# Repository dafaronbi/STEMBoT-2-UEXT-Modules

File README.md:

# STEMBoT-2-UEXT-Modules

## PREPARED BY
### Dean Harris, Daniel Faronbi,
### Dylan Schufeldt, Houd Al-Shariyani

The STEMBoT 2 (SB2)  is a mobile robotic platform and successor to SBI’s first product, the CEENBoT, which 
saw success in schools throughout the United States. The development goal of the SB2 project is to create a 
modular and easy-to-use product that will be used as a platform for teaching STEM related skills to students 
from kindergarten to the university level. The SB2 will accomplish this goal by incorporating the Python programming 
language into embedded systems development. The SB2 also uses plug-and-play UEXT modules for customizability and increased functionality.

The goal of this Capstone team will be to develop seven UEXT modules with a Python library for use by STEMBoT Incorporated. This document
will go over general requirements for the batch of UEXT modules as well as the specifications for each individual module. Necessary changes
to these specifications should be requested prior to completion of the project.

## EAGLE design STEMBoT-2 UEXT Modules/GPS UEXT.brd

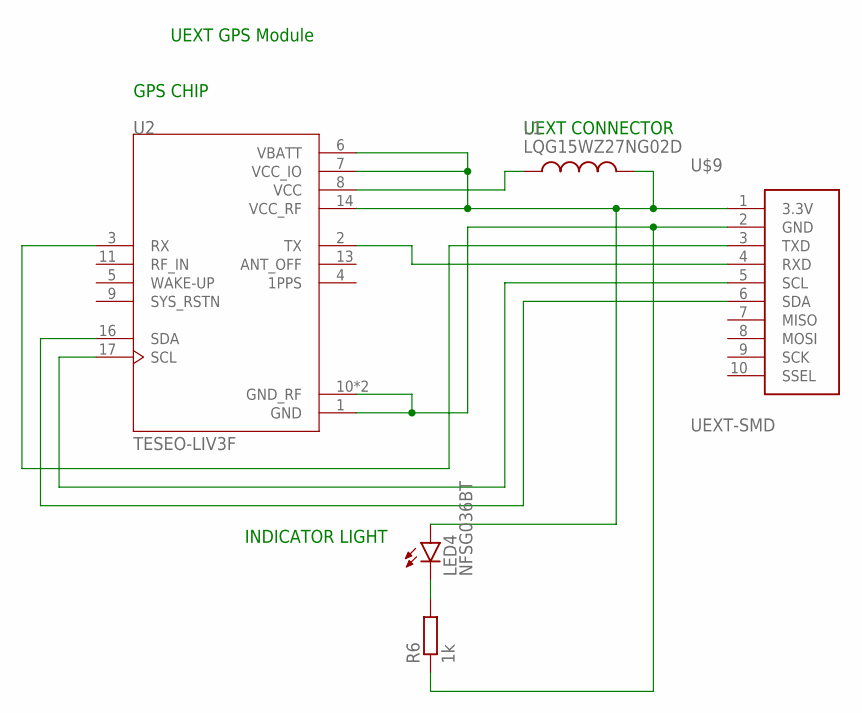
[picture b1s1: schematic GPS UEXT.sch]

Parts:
L1: LQG15WZ27NG02D; INDC1006X60N
LED4: NFSG036BT
R6: 1k; M1206
U2: TESEO-LIV3F
U$9: UEXT-SMD

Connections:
unnamed: U2.2 (TX), U$9.4 (RXD)
unnamed: U2.3 (RX), U$9.3 (TXD)
unnamed: L1.1, U2.8 (VCC)
unnamed: R6.1, U2.1 (GND), U2.10 (GND_RF), U2.12 (GND_RF), U$9.2 (GND)
unnamed: L1.2, LED4.A, U2.6 (VBATT), U2.7 (VCC_IO), U2.14 (VCC_RF), U$9.1 (3.3V)
unnamed: U2.17 (SCL), U$9.5 (SCL)
unnamed: U2.16 (SDA), U$9.6 (SDA)
unnamed: LED4.C, R6.2

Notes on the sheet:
GPS CHIP
UEXT CONNECTOR
INDICATOR LIGHT
UEXT GPS Module

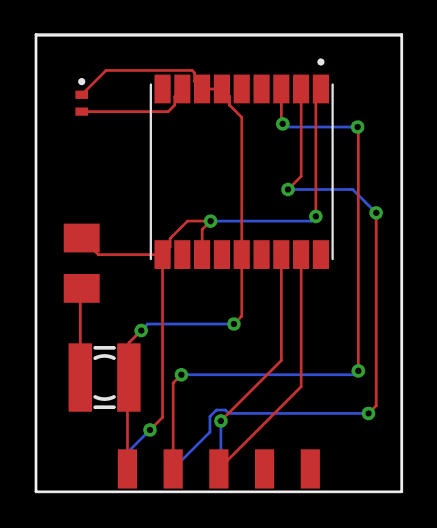
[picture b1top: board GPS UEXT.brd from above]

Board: 2 copper layers, 20.3 x 25.3 mm, 5 parts (0 on the bottom side), 8 nets.

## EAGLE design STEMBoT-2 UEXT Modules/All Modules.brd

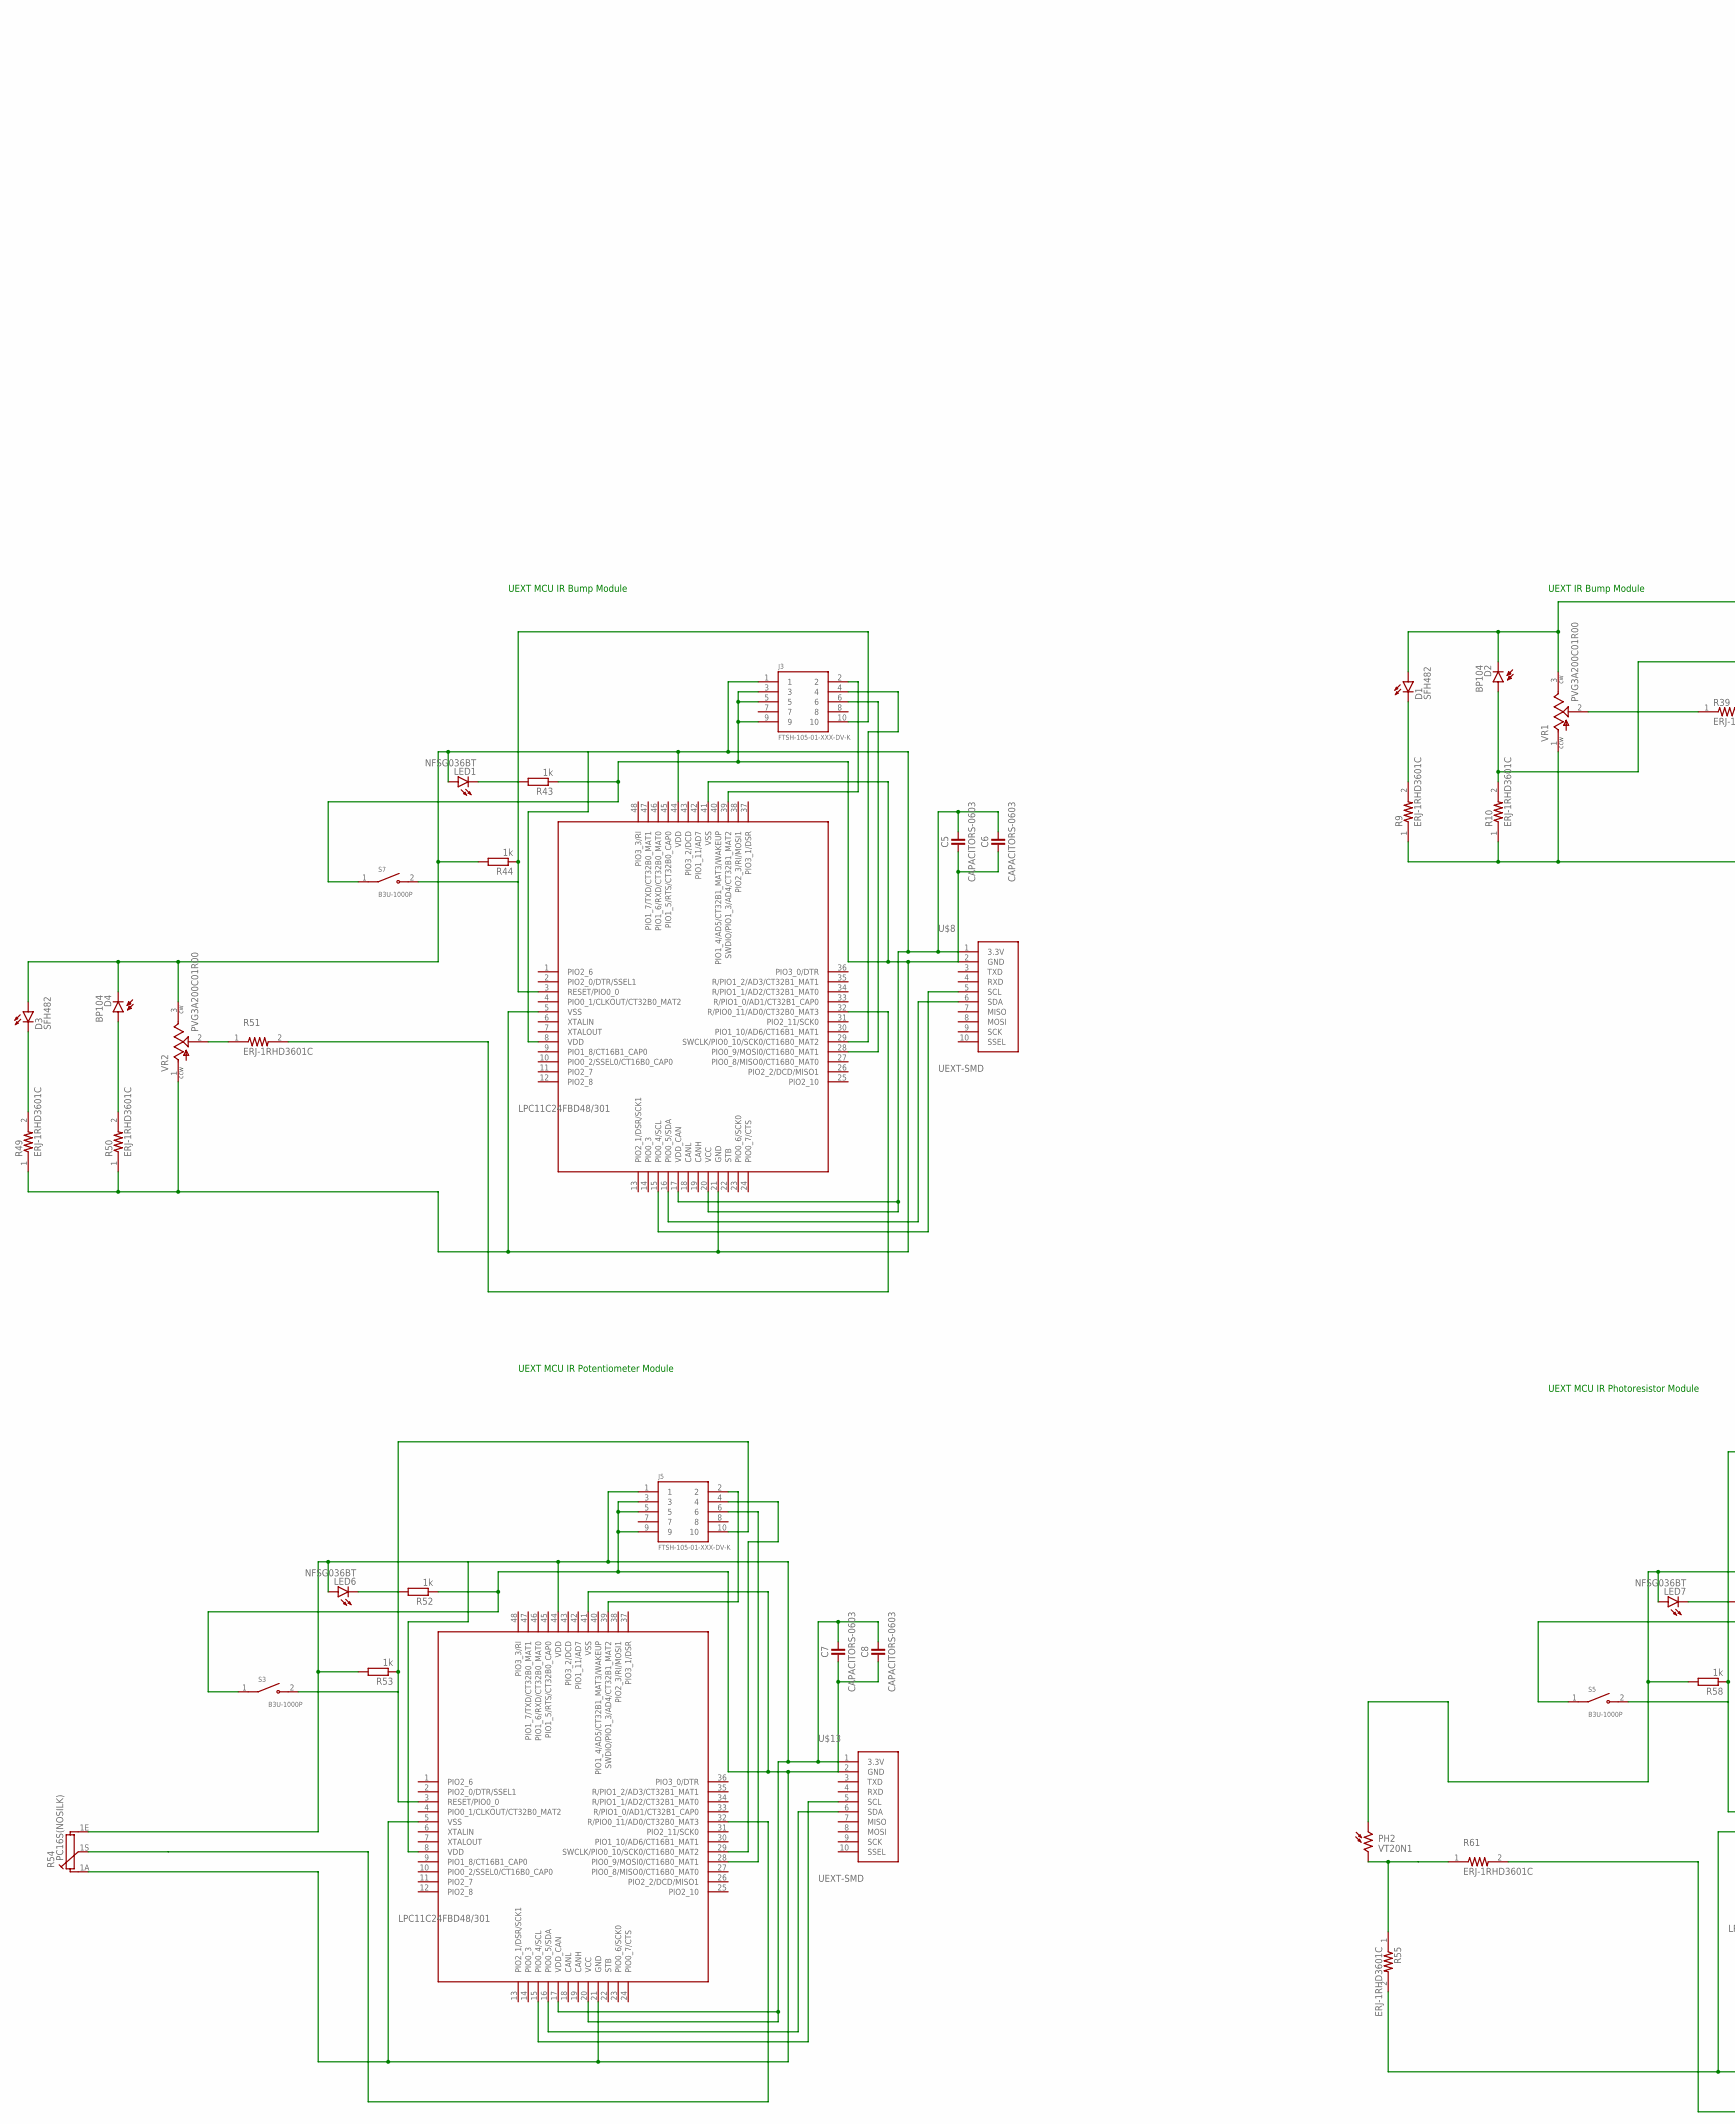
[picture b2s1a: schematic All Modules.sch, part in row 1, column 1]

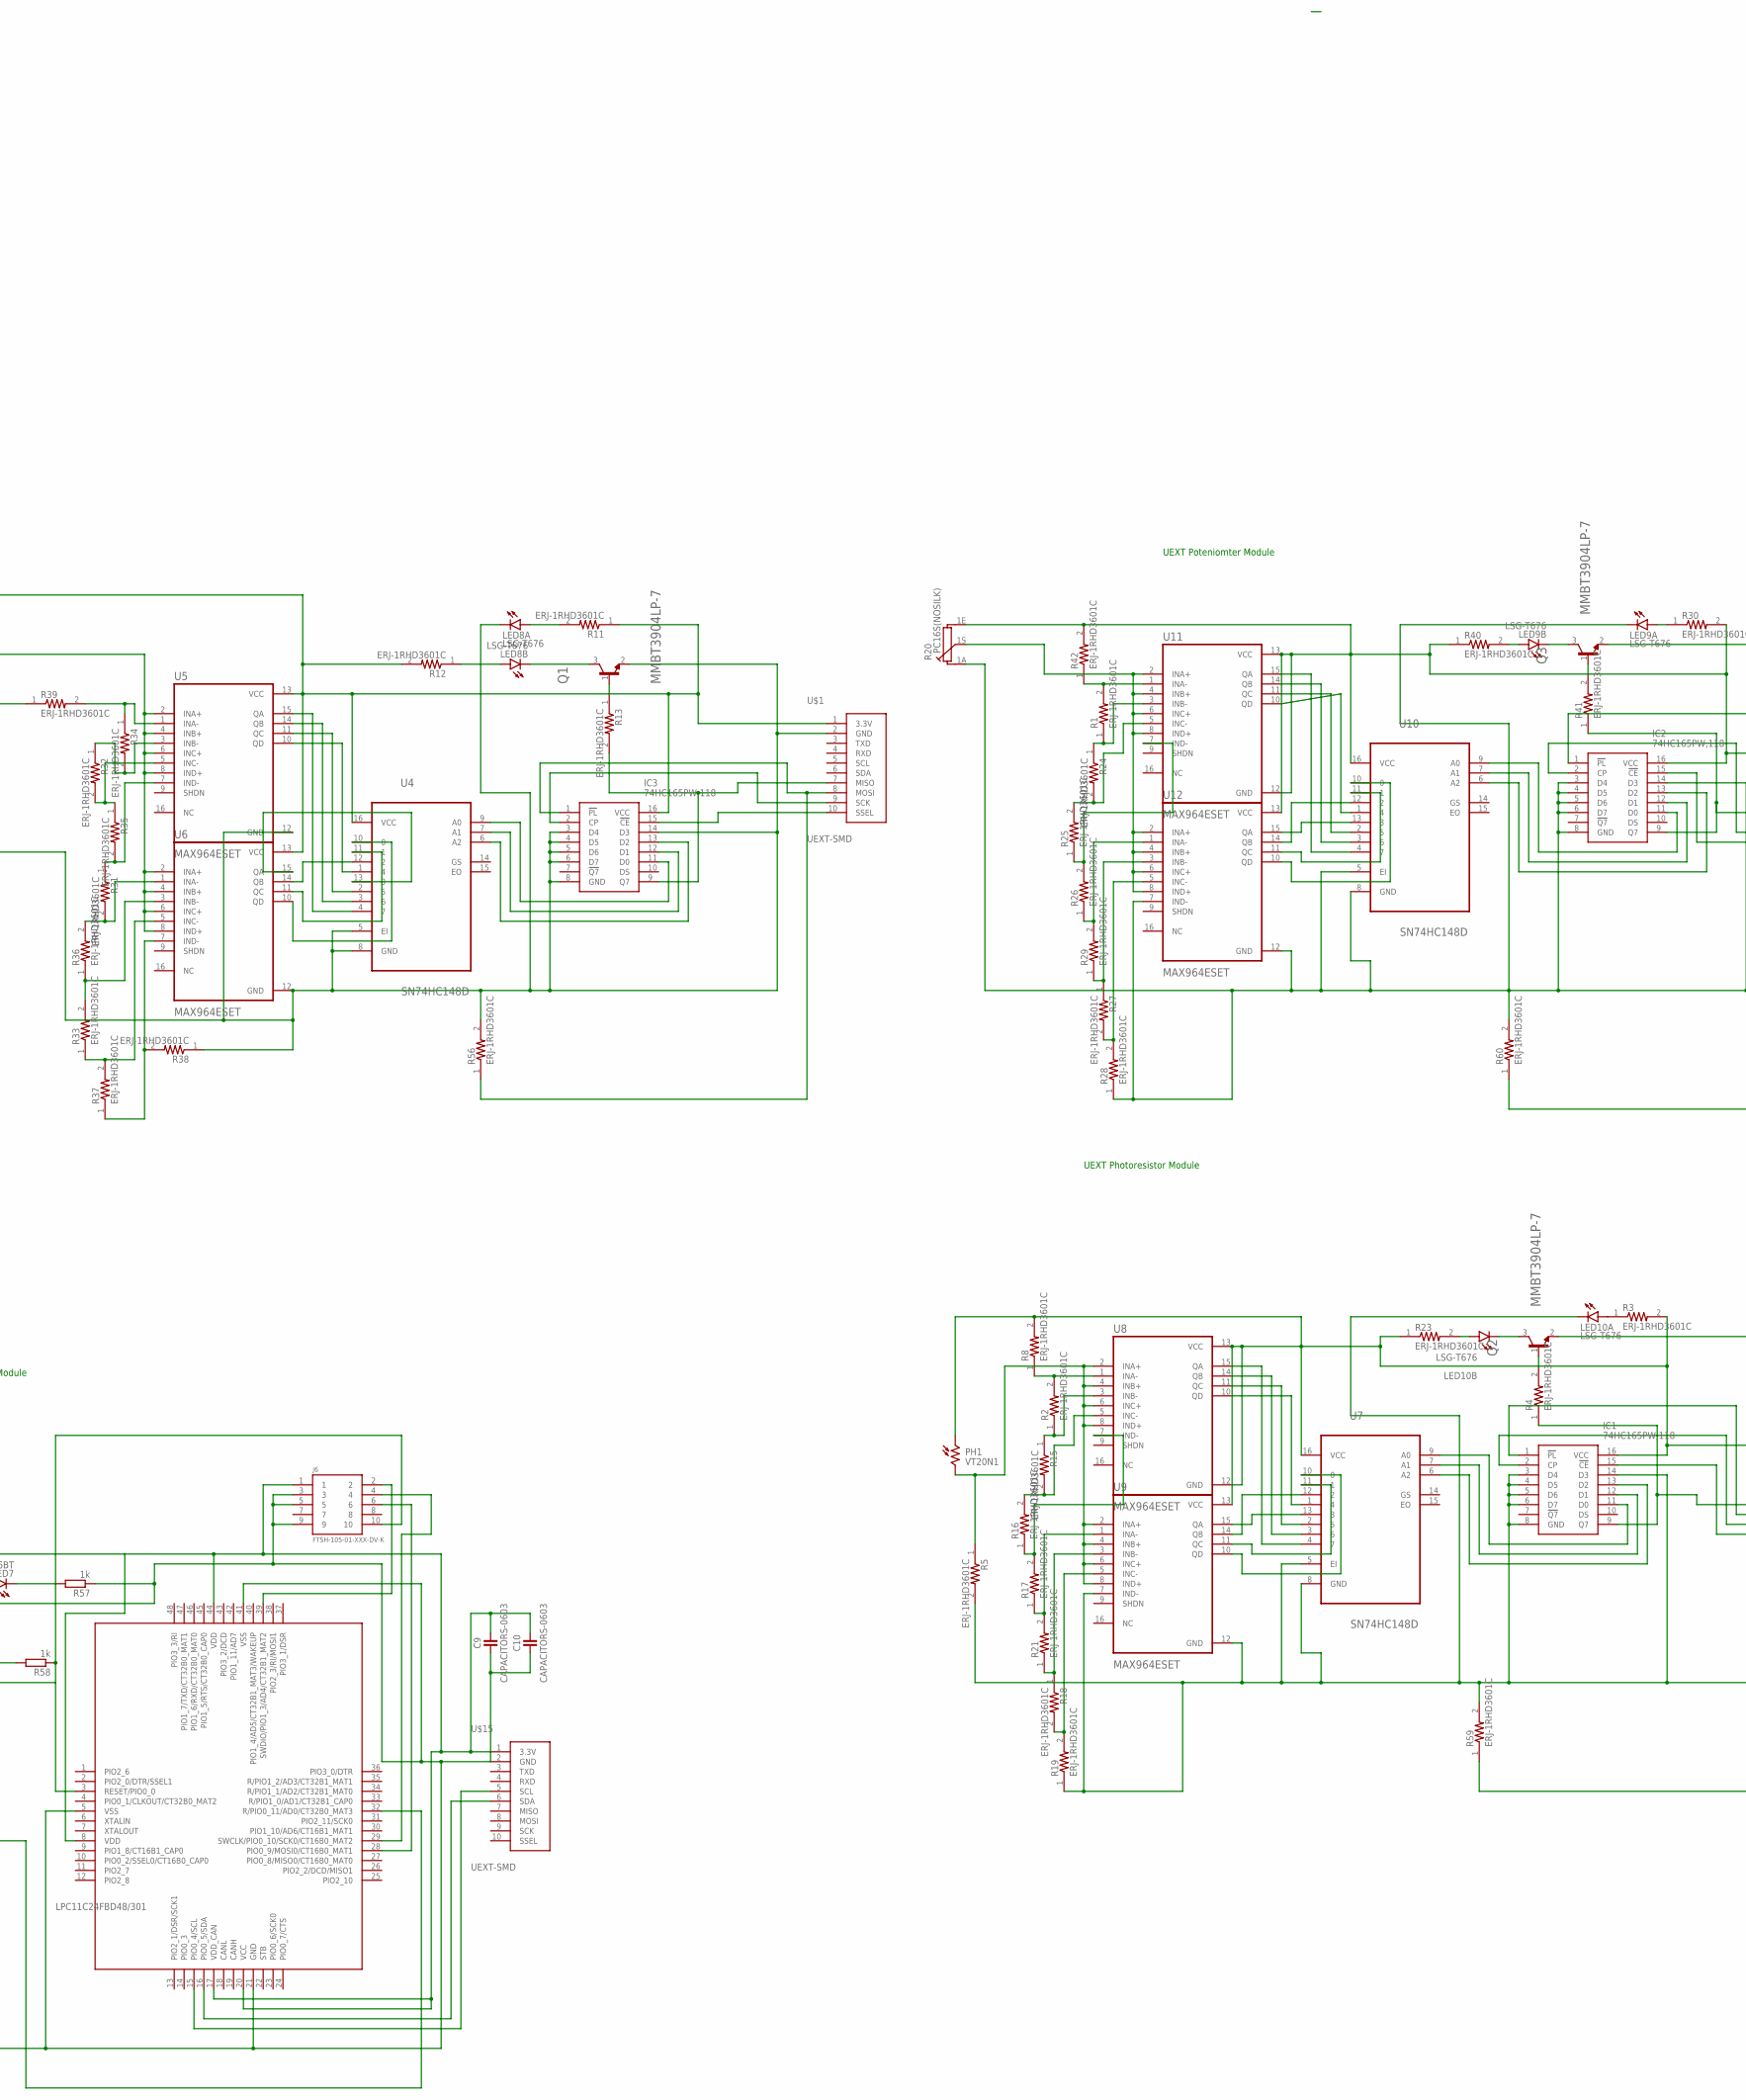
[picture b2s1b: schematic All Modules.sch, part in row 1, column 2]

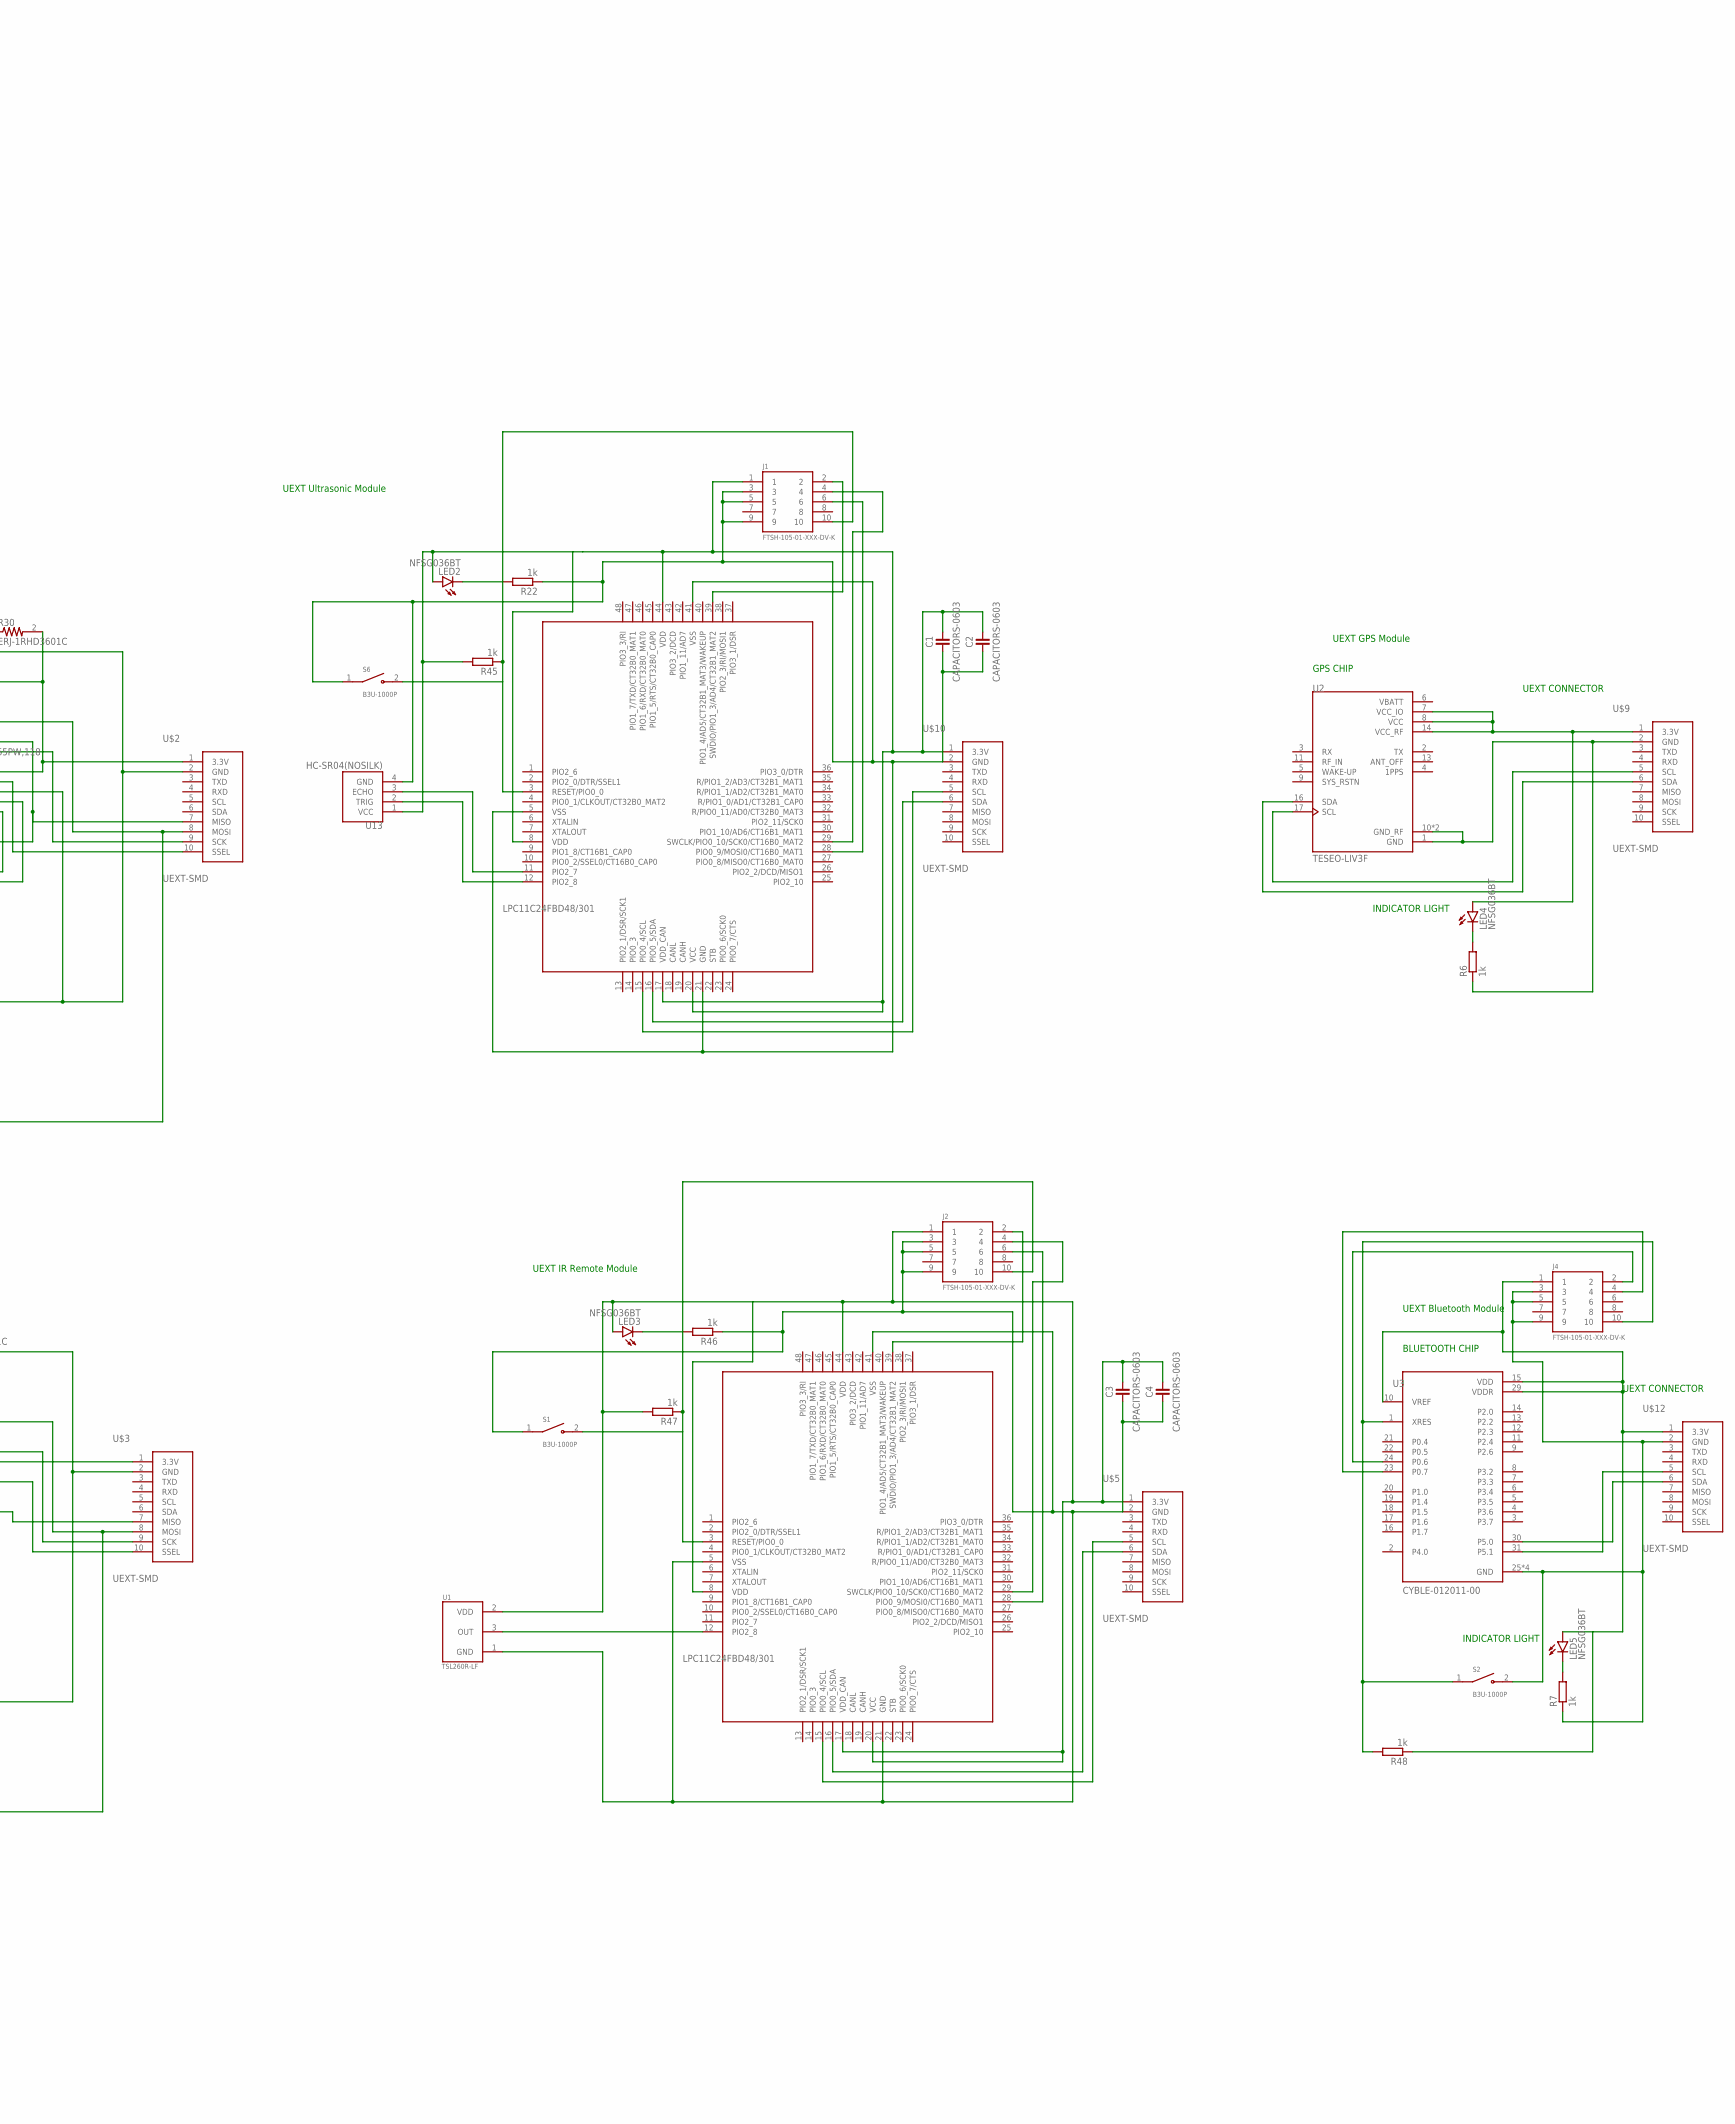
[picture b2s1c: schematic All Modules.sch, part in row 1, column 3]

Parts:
C1, C2, C3, C4, C5, C6, C7, C8, C9, C10: CAPACITORS-0603; C0603
D1, D3: SFH482
D2, D4: BP104
IC1, IC2, IC3: 74HC165PW,118; SOP65P640X110-16N
J1, J2, J3, J4, J5, J6: FTSH-105-01-XXX-DV-K
LED1, LED2, LED3, LED4, LED5, LED6, LED7: NFSG036BT
LED8, LED9, LED10: LSG-T676; P-LCC4-0
PH1, PH2: VT20N1; TO46-VT200
Q1, Q2, Q3: MMBT3904LP-7; DFN101X61X53-3N
R1, R2, R3, R4, R5, R8, R9, R10, R11, R12, R13, R15, R16, R17, R18, R19, R21, R23, R24, R25, R26, R27, R28, R29, R30, R31, R32, R33, R34, R35, R36, R37, R38, R39, R40, R41, R42, R49, R50, R51, R55, R56, R59, R60, R61: ERJ-1RHD3601C; RESC0603X26N
R6, R7, R22, R43, R44, R45, R46, R47, R48, R52, R53, R57, R58: 1k; M1206
R20, R54: PC16S(NOSILK)
S1, S2, S3, S5, S6, S7: B3U-1000P; SW_B3U-1000P
U1: TSL260R-LF; XDCR_TSL260R-LF
U2: TESEO-LIV3F
U3: CYBLE-012011-00; XCVR_CYBLE-012011-00
U4, U7, U10: SN74HC148D; SOIC127P600X175-16N
U5, U6, U8, U9, U11, U12: MAX964ESET; SOIC127P600X175-16N
U13: HC-SR04(NOSILK); XCVR_HC-SR04(NOSILK)
U$1, U$2, U$3, U$5, U$8, U$9, U$10, U$12, U$13, U$15: UEXT-SMD
U$4, U$6, U$7, U$11, U$14: LPC11C24FBD48/301; QFP50P900X900X160-48N
VR1, VR2: PVG3A200C01R00; TRIM_PVG3A200C01R00

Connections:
unnamed: C1.1, C2.1, J1.3, J1.5, J1.9, R22.1, S6.1, U13.4 (GND), U$7.5 (VSS), U$7.21 (GND), U$7.41 (VSS), U$10.2 (GND)
unnamed: D1.A, D2.K (C), IC3.16 (VCC), R11.1, R12.2, U4.16 (VCC), U5.13 (VCC), U6.13 (VCC), U$1.1 (3.3V), VR1.3 (CW)
unnamed: LED2.C, R22.2
unnamed: Q3.1 (B), R41.2
unnamed: LED9.2 (A), R30.1
unnamed: C3.1, C4.1, J2.3, J2.5, J2.9, R46.1, S1.1, U1.1 (GND), U$4.5 (VSS), U$4.21 (GND), U$4.41 (VSS), U$5.2 (GND)
unnamed: IC3.15 (!CE), U$1.10 (SSEL)
unnamed: Q2.1 (B), R4.2
unnamed: LED10.2 (A), R3.1
unnamed: LED10.3 (C), Q2.3 (C)
unnamed: IC1.13 (D2), U7.6 (A2)
unnamed: PH1.2, R5.1, U8.2 (INA+), U8.4 (INB+), U8.6 (INC+), U8.8 (IND+), U9.2 (INA+), U9.4 (INB+), U9.6 (INC+), U9.8 (IND+)
unnamed: IC1.15 (!CE), U$3.10 (SSEL)
unnamed: IC3.2 (CP), U$1.9 (SCK)
unnamed: LED9.3 (C), Q3.3 (C)
unnamed: IC1.9 (Q7), R4.1, U$3.7 (MISO)
unnamed: IC2.11 (D0), U10.9 (A0)
unnamed: LED10.4 (A), R23.2
unnamed: IC1.11 (D0), U7.9 (A0)
unnamed: IC1.12 (D1), U7.7 (A1)
unnamed: R6.1, U2.1 (GND), U2.10 (GND_RF), U2.12 (GND_RF), U$9.2 (GND)
unnamed: LED4.A, U2.7 (VCC_IO), U2.8 (VCC), U2.14 (VCC_RF), U$9.1 (3.3V)
unnamed: U2.17 (SCL), U$9.5 (SCL)
unnamed: U2.16 (SDA), U$9.6 (SDA)
unnamed: LED4.C, R6.2
unnamed: J4.1, LED5.A, R48.1, U3.10 (VREF), U3.15 (VDD), U3.29 (VDDR), U$12.1 (3.3V)
unnamed: U3.30 (P5.0), U$12.6 (SDA)
unnamed: U3.31 (P5.1), U$12.5 (SCL)
unnamed: J4.3, J4.5, J4.9, R7.1, S2.2, U3.25 (GND), U3.26 (GND), U3.27 (GND), U3.28 (GND), U$12.2 (GND)
unnamed: LED5.C, R7.2
unnamed: D1.K (C), R9.2
unnamed: LED8.2 (A), R11.2
unnamed: R2.1, R15.1, U8.3 (INB-)
unnamed: R15.2, R16.2, U8.5 (INC-)
unnamed: R16.1, R17.2, U8.7 (IND-)
unnamed: R17.1, R21.2, U9.1 (INA-)
unnamed: R18.1, R21.1, U9.3 (INB-)
unnamed: R18.2, R19.2, U9.5 (INC-)
unnamed: IC1.3 (D4), IC1.4 (D5), IC1.5 (D6), IC1.6 (D7), IC1.8 (GND), IC1.14 (D3), LED10.1 (C), Q2.2 (E), R5.2, R19.1, R59.2, U7.5 (EI), U7.8 (GND), U9.7 (IND-), U9.12 (GND), U$3.2 (GND)
unnamed: U7.4 (7), U8.15 (QA)
unnamed: U7.3 (6), U8.14 (QB)
unnamed: U7.2 (5), U8.11 (QC)
unnamed: U7.1 (4), U8.10 (QD)
unnamed: U7.13 (3), U9.15 (QA)
unnamed: U7.12 (2), U9.14 (QB)
unnamed: LED8.4 (A), R12.1
unnamed: LED8.3 (C), Q1.3 (C)
unnamed: U7.11 (1), U9.11 (QC)
unnamed: U7.10 (0), U9.10 (QD)
unnamed: R2.2, R8.1, U8.1 (INA-)
unnamed: IC1.16 (VCC), PH1.1, R3.2, R8.2, R23.1, U7.16 (VCC), U8.12 (GND), U8.13 (VCC), U9.13 (VCC), U$3.1 (3.3V)
unnamed: IC1.2 (CP), U$3.9 (SCK)
unnamed: IC2.12 (D1), U10.7 (A1)
unnamed: IC2.13 (D2), U10.6 (A2)
unnamed: IC3.3 (D4), IC3.4 (D5), IC3.5 (D6), IC3.6 (D7), IC3.8 (GND), IC3.14 (D3), LED8.1 (C), Q1.2 (E), R9.1, R10.1, R38.1, R56.2, U4.5 (EI), U4.8 (GND), U5.12 (GND), U6.12 (GND), U$1.2 (GND), VR1.1 (CCW)
unnamed: IC2.9 (Q7), R41.1, U$2.7 (MISO)
unnamed: LED9.4 (A), R40.2
unnamed: R1.1, R24.1, U11.3 (INB-)
unnamed: R24.2, R25.2, U11.5 (INC-)
unnamed: R25.1, R26.2, U11.7 (IND-)
unnamed: R26.1, R29.2, U12.1 (INA-)
unnamed: R27.1, R29.1, U12.3 (INB-)
unnamed: R27.2, R28.2, U12.5 (INC-)
unnamed: IC2.3 (D4), IC2.4 (D5), IC2.5 (D6), IC2.6 (D7), IC2.8 (GND), IC2.14 (D3), LED9.1 (C), Q3.2 (E), R20.1A, R28.1, R60.2, U10.5 (EI), U10.8 (GND), U12.7 (IND-), U12.12 (GND), U$2.2 (GND)
unnamed: U10.4 (7), U11.15 (QA)
unnamed: U10.3 (6), U11.14 (QB)
unnamed: U10.2 (5), U11.11 (QC)
unnamed: U10.1 (4), U11.10 (QD)
unnamed: U10.13 (3), U12.15 (QA)
unnamed: D2.A, R10.2, U5.2 (INA+), U5.4 (INB+), U5.6 (INC+), U5.8 (IND+), U6.2 (INA+), U6.4 (INB+), U6.6 (INC+), U6.8 (IND+)
unnamed: Q1.1 (B), R13.1
unnamed: U10.12 (2), U12.14 (QB)
unnamed: IC3.11 (D0), U4.9 (A0)
unnamed: IC3.12 (D1), U4.7 (A1)
unnamed: IC3.13 (D2), U4.6 (A2)
unnamed: IC3.9 (Q7), R13.2, U$1.7 (MISO)
unnamed: U10.11 (1), U12.11 (QC)
unnamed: R34.1, R39.2, U5.1 (INA-)
unnamed: U$7.16 (PIO0_5/SDA), U$10.6 (SDA)
unnamed: U$7.15 (PIO0_4/SCL), U$10.5 (SCL)
unnamed: R32.1, R34.2, U5.3 (INB-)
unnamed: J1.4, U$7.29 (SWCLK/PIO0_10/SCK0/CT16B0_MAT2)
unnamed: J1.2, U$7.39 (SWDIO/PIO1_3/AD4/CT32B1_MAT2)
unnamed: J1.6, U$7.28 (PIO0_9/MOSI0/CT16B0_MAT1)
unnamed: U13.2 (TRIG), U$7.12 (PIO2_8)
unnamed: U13.3 (ECHO), U$7.11 (PIO2_7)
unnamed: R32.2, R35.1, U5.5 (INC-)
unnamed: R31.1, R35.2, U5.7 (IND-)
unnamed: R31.2, R36.2, U6.1 (INA-)
unnamed: R33.2, R36.1, U6.3 (INB-)
unnamed: R33.1, R37.2, U6.5 (INC-)
unnamed: R37.1, R38.2, U6.7 (IND-)
unnamed: U4.4 (7), U5.15 (QA)
unnamed: U4.3 (6), U5.14 (QB)
unnamed: U4.2 (5), U5.11 (QC)
unnamed: U4.1 (4), U5.10 (QD)
unnamed: U4.13 (3), U6.15 (QA)
unnamed: U4.12 (2), U6.14 (QB)
unnamed: U4.11 (1), U6.11 (QC)
unnamed: U4.10 (0), U6.10 (QD)
unnamed: U10.10 (0), U12.10 (QD)
unnamed: R1.2, R42.1, U11.1 (INA-)
unnamed: IC2.15 (!CE), U$2.10 (SSEL)
unnamed: IC2.2 (CP), U$2.9 (SCK)
unnamed: IC2.16 (VCC), R20.1E, R30.2, R40.1, R42.2, U10.16 (VCC), U11.12 (GND), U11.13 (VCC), U12.13 (VCC), U$2.1 (3.3V)
unnamed: R20.1S, U11.2 (INA+), U11.4 (INB+), U11.6 (INC+), U11.8 (IND+), U12.2 (INA+), U12.4 (INB+), U12.6 (INC+), U12.8 (IND+)
unnamed: LED6.C, R52.2
unnamed: LED1.C, R43.2
unnamed: J1.10, R45.1, S6.2, U$7.3 (RESET/PIO0_0)
unnamed: C1.2, C2.2, J1.1, LED2.A, R45.2, U13.1 (VCC), U$7.8 (VDD), U$7.17 (VDD_CAN), U$7.20 (VCC), U$7.44 (VDD), U$10.1 (3.3V)
unnamed: J4.10, R48.2, S2.1, U3.1 (XRES)
unnamed: LED3.C, R46.2
unnamed: U$11.16 (PIO0_5/SDA), U$13.6 (SDA)
unnamed: U$4.16 (PIO0_5/SDA), U$5.6 (SDA)
unnamed: U$4.15 (PIO0_4/SCL), U$5.5 (SCL)
unnamed: C3.2, C4.2, J2.1, LED3.A, R47.2, U1.2 (VDD), U$4.8 (VDD), U$4.17 (VDD_CAN), U$4.20 (VCC), U$4.44 (VDD), U$5.1 (3.3V)
unnamed: J2.4, U$4.29 (SWCLK/PIO0_10/SCK0/CT16B0_MAT2)
unnamed: U$6.16 (PIO0_5/SDA), U$8.6 (SDA)
unnamed: J2.2, U$4.39 (SWDIO/PIO1_3/AD4/CT32B1_MAT2)
unnamed: J2.6, U$4.28 (PIO0_9/MOSI0/CT16B0_MAT1)
unnamed: U$6.15 (PIO0_4/SCL), U$8.5 (SCL)
unnamed: U1.3 (OUT), U$4.12 (PIO2_8)
unnamed: J4.2, U3.24 (P0.6)
unnamed: J2.10, R47.1, S1.2, U$4.3 (RESET/PIO0_0)
unnamed: J4.4, U3.23 (P0.7)
unnamed: J3.4, U$6.29 (SWCLK/PIO0_10/SCK0/CT16B0_MAT2)
unnamed: J3.2, U$6.39 (SWDIO/PIO1_3/AD4/CT32B1_MAT2)
unnamed: J3.6, U$6.28 (PIO0_9/MOSI0/CT16B0_MAT1)
unnamed: D3.K (C), R49.2
unnamed: D4.A, R50.2
unnamed: R51.1, VR2.2 (WIPER)
unnamed: J3.10, R44.1, S7.2, U$6.3 (RESET/PIO0_0)
unnamed: R51.2, U$6.32 (R/PIO0_11/AD0/CT32B0_MAT3)
unnamed: C5.1, C6.1, J3.3, J3.5, J3.9, R43.1, R49.1, R50.1, S7.1, U$6.5 (VSS), U$6.21 (GND), U$6.41 (VSS), U$8.2 (GND), VR2.1 (CCW)
unnamed: C5.2, C6.2, D3.A, D4.K (C), J3.1, LED1.A, R44.2, U$6.8 (VDD), U$6.17 (VDD_CAN), U$6.20 (VCC), U$6.44 (VDD), U$8.1 (3.3V), VR2.3 (CW)
unnamed: U$11.15 (PIO0_4/SCL), U$13.5 (SCL)
unnamed: J5.4, U$11.29 (SWCLK/PIO0_10/SCK0/CT16B0_MAT2)
unnamed: J5.2, U$11.39 (SWDIO/PIO1_3/AD4/CT32B1_MAT2)
unnamed: J5.6, U$11.28 (PIO0_9/MOSI0/CT16B0_MAT1)
unnamed: J5.10, R53.1, S3.2, U$11.3 (RESET/PIO0_0)
unnamed: C7.1, C8.1, J5.3, J5.5, J5.9, R52.1, R54.1A, S3.1, U$11.5 (VSS), U$11.21 (GND), U$11.41 (VSS), U$13.2 (GND)
unnamed: R39.1, VR1.2 (WIPER)
unnamed: C9.2, C10.2, J6.1, LED7.A, PH2.1, R58.2, U$14.8 (VDD), U$14.17 (VDD_CAN), U$14.20 (VCC), U$14.44 (VDD), U$15.1 (3.3V)
unnamed: C7.2, C8.2, J5.1, LED6.A, R53.2, R54.1E, U$11.8 (VDD), U$11.17 (VDD_CAN), U$11.20 (VCC), U$11.44 (VDD), U$13.1 (3.3V)
unnamed: LED7.C, R57.2
unnamed: U$14.16 (PIO0_5/SDA), U$15.6 (SDA)
unnamed: U$14.15 (PIO0_4/SCL), U$15.5 (SCL)
unnamed: J6.4, U$14.29 (SWCLK/PIO0_10/SCK0/CT16B0_MAT2)
unnamed: J6.2, U$14.39 (SWDIO/PIO1_3/AD4/CT32B1_MAT2)
unnamed: J6.6, U$14.28 (PIO0_9/MOSI0/CT16B0_MAT1)
unnamed: J6.10, R58.1, S5.2, U$14.3 (RESET/PIO0_0)
unnamed: PH2.2, R55.1, R61.1
unnamed: IC3.1 (!PL), R56.1, U$1.8 (MOSI)
unnamed: R61.2, U$14.32 (R/PIO0_11/AD0/CT32B0_MAT3)
unnamed: C9.1, C10.1, J6.3, J6.5, J6.9, R55.2, R57.1, S5.1, U$14.5 (VSS), U$14.21 (GND), U$14.41 (VSS), U$15.2 (GND)
unnamed: IC1.1 (!PL), R59.1, U$3.8 (MOSI)
unnamed: IC2.1 (!PL), R60.1, U$2.8 (MOSI)
VBATT: U2.6 (VBATT)

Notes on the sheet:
UEXT Ultrasonic Module
GPS CHIP
UEXT CONNECTOR
INDICATOR LIGHT
UEXT GPS Module
BLUETOOTH CHIP
UEXT Bluetooth Module
UEXT Photoresistor Module
UEXT Poteniomter Module
UEXT IR Remote Module
UEXT IR Bump Module
UEXT MCU IR Bump Module
UEXT MCU IR Potentiometer Module
UEXT MCU IR Photoresistor Module
